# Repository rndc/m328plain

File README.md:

m328plain
=========

Plain Simple ATmega328(P) Development Board. Warning! this board is for testing purpose ONLY! Use at your own risk.

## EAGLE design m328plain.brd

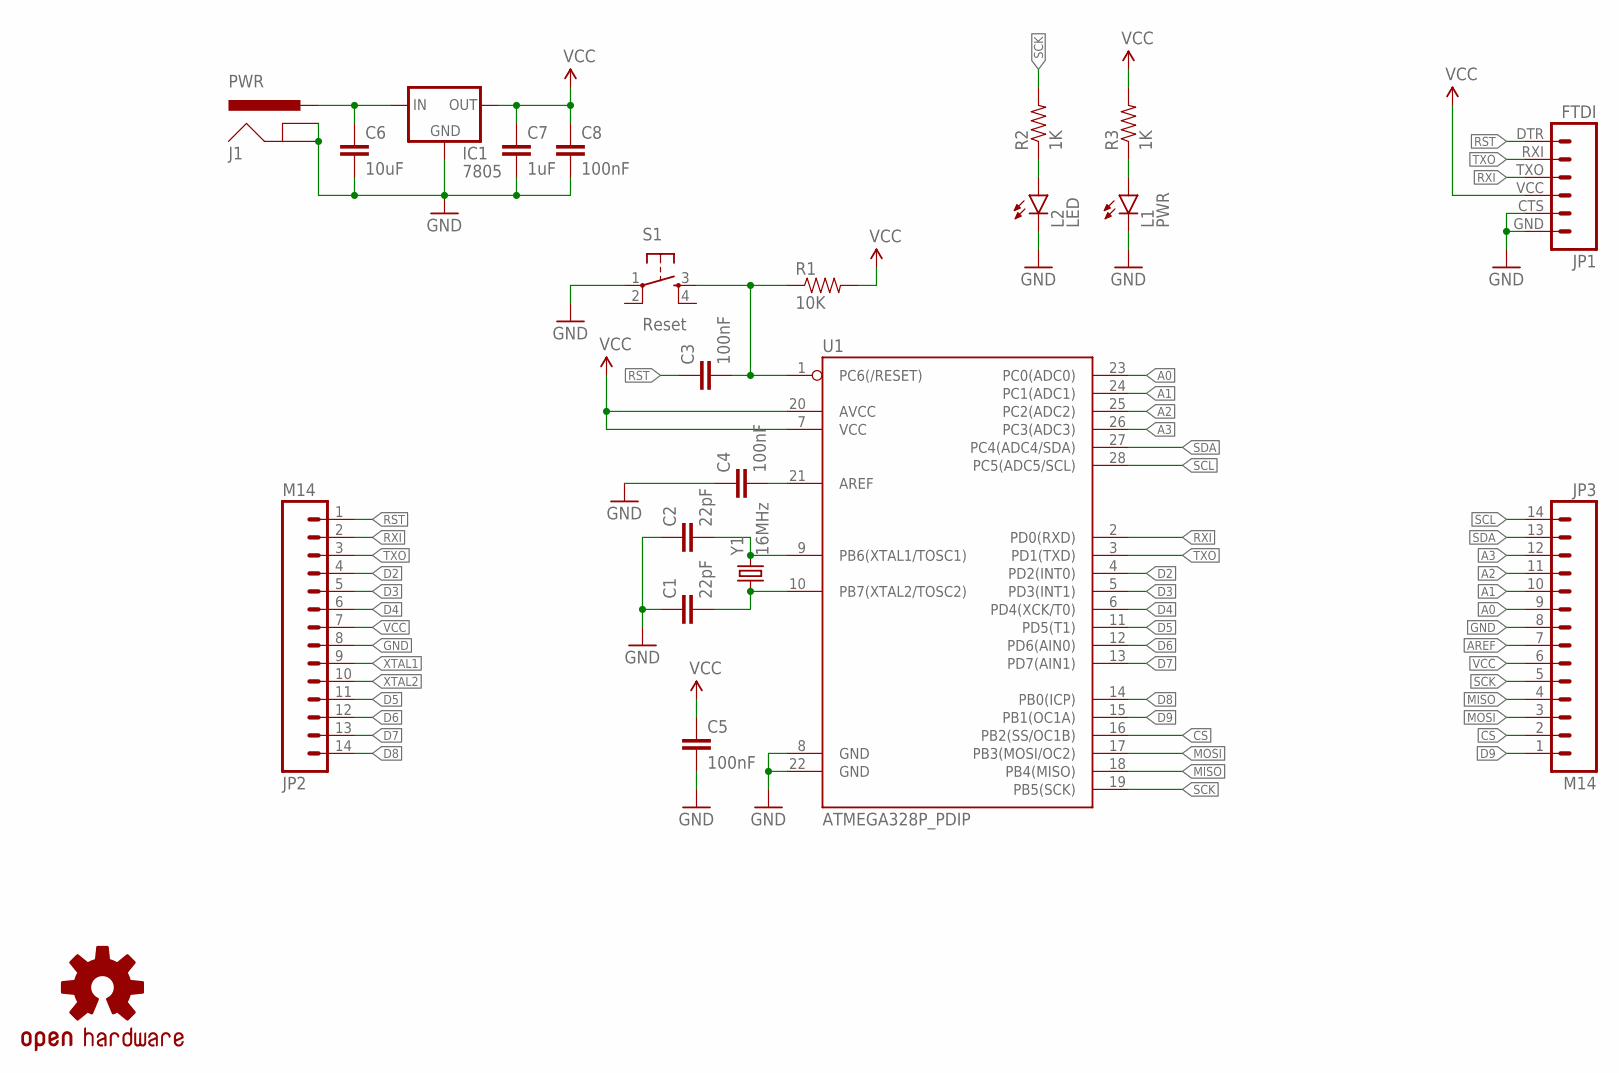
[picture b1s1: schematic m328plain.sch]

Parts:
C1, C2: 22pF; 0805
C3, C4, C5, C8: 100nF; 0805
C6: 10uF; 0603-CAP
C7: 1uF; 0603-CAP
IC1: 7805; TO-92
J1: PWR; POWER_JACK_PTH
JP1: FTDI; FTDI_BASIC
JP2, JP3: M14; 1X14
L1: PWR; LED3MM-NS
L2: LED; LED3MM-NS
LOGO1: OSHW-LOGOL; OSHW-LOGO-L
R1: 10K; 0603-RES
R2, R3: 1K; 0603-RES
S1: Reset; TACTILE-PTH
U1: ATMEGA328P_PDIP; DIL28-3
Y1: 16MHz; HC49US

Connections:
A0: JP3.9, U1.23 (PC0(ADC0))
A1: JP3.10, U1.24 (PC1(ADC1))
A2: JP3.11, U1.25 (PC2(ADC2))
A3: JP3.12, U1.26 (PC3(ADC3))
AREF: C4.2, JP3.7, U1.21 (AREF)
CS: JP3.2, U1.16 (PB2(SS/OC1B))
D2: JP2.4, U1.4 (PD2(INT0))
D3: JP2.5, U1.5 (PD3(INT1))
D4: JP2.6, U1.6 (PD4(XCK/T0))
D5: JP2.11, U1.11 (PD5(T1))
D6: JP2.12, U1.12 (PD6(AIN0))
D7: JP2.13, U1.13 (PD7(AIN1))
D8: JP2.14, U1.14 (PB0(ICP))
D9: JP3.1, U1.15 (PB1(OC1A))
GND: C1.1, C2.1, C4.1, C5.2, C6.2, C7.2, C8.2, IC1.1 (GND), J1.GND, J1.GNDBREAK, JP1.CTS (5), JP1.GND (6), JP2.8, JP3.8, L1.K (C), L2.K (C), S1.1, U1.8 (GND), U1.22 (GND)
MISO: JP3.4, U1.18 (PB4(MISO))
MOSI: JP3.3, U1.17 (PB3(MOSI/OC2))
unnamed: C3.2, R1.1, S1.3, U1.1 (PC6(/RESET))
unnamed: C6.1, IC1.2 (IN), J1.PWR
unnamed: L1.A, R3.1
unnamed: L2.A, R2.1
RST: C3.1, JP1.DTR (1), JP2.1
RXI: JP1.TXO (3), JP2.2, U1.2 (PD0(RXD))
SCK: JP3.5, R2.2, U1.19 (PB5(SCK))
SCL: JP3.14, U1.28 (PC5(ADC5/SCL))
SDA: JP3.13, U1.27 (PC4(ADC4/SDA))
TXO: JP1.RXI (2), JP2.3, U1.3 (PD1(TXD))
VCC: C5.1, C7.1, C8.1, IC1.3 (OUT), JP1.VCC (4), JP2.7, JP3.6, R1.2, R3.2, U1.7 (VCC), U1.20 (AVCC)
XTAL1: C2.2, JP2.9, U1.9 (PB6(XTAL1/TOSC1)), Y1.2
XTAL2: C1.2, JP2.10, U1.10 (PB7(XTAL2/TOSC2)), Y1.1

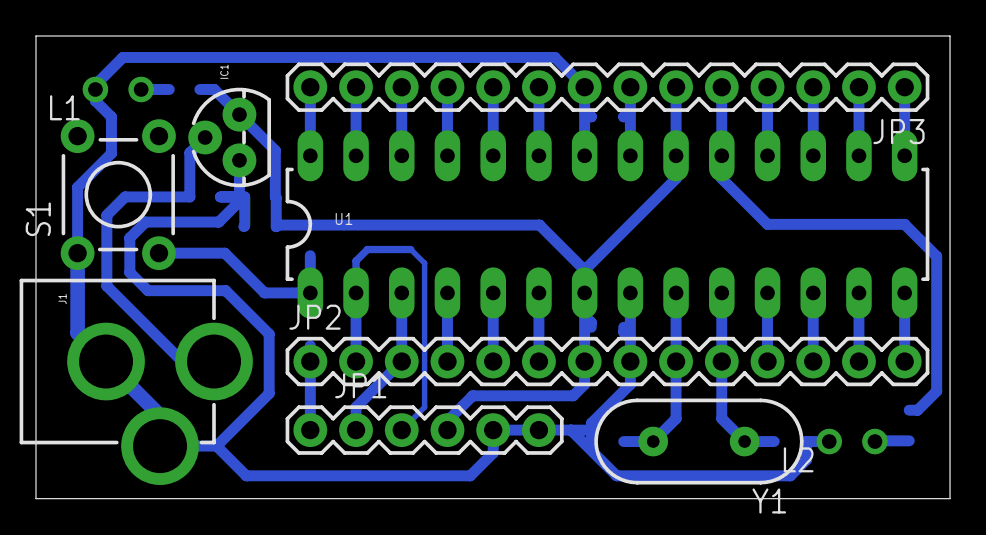
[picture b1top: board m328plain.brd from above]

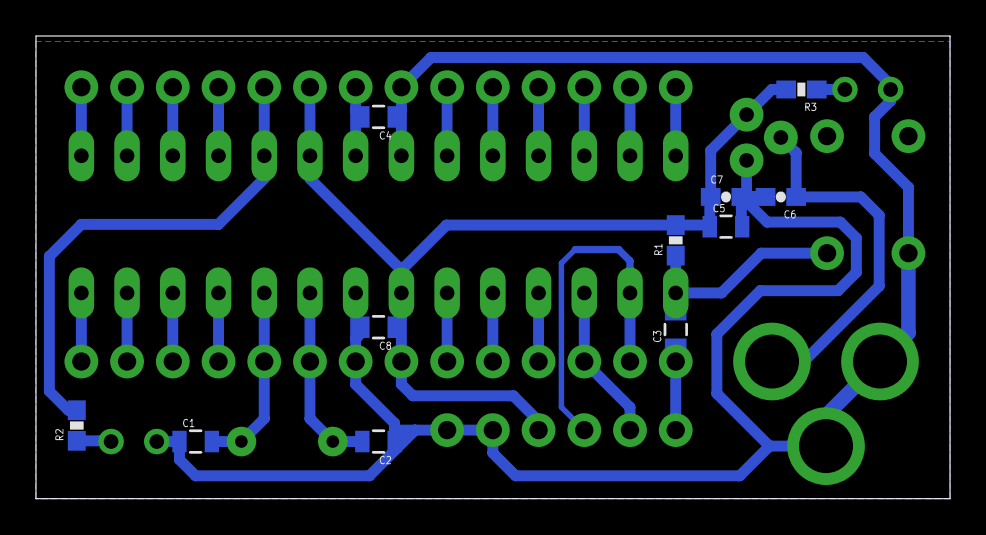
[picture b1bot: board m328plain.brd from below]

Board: 2 copper layers, 50.8 x 25.7 mm, 21 parts (11 on the bottom side), 30 nets.

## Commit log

2014-10-25 CERN license
2014-10-25 Added board layout
2014-10-25 Fixed board layout image
2015-01-30 :sparkles: new board layout

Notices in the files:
parts and their libraries:
SparkFun-Capacitors: Licensing: Creative Commons ShareAlike 4.0 International - https://creativecommons.org/licenses/by-sa/4.0
